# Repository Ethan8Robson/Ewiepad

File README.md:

# Ewiepad

A 6 key macropad built using an Arduino micro.

## Features
### PCB
Hot swappable switches through mill-max sockets
<br> Arduino Micro
<br> 3d printable case

### Case
Screws aren't visible on the front
<br> Flush design

## Parts List
1 Printed case (top + bottom)
<br> 1 PCB
<br> 1 Arduino micro
<br> 2 Screws of any kind as long as they fit
<br> 6 Bumpons to put on the bottom of the case
<br> 6 mechanical switches of any kind
<br> 12 mill max hotswap sockets

## Assembly
### Assembling the PCB
1 - First, gather the Arduino micro and PCB. They must be assembled together
<br> 2 - The Arduino must be placed UNDERNEATH the pcb, meaning it will be facing upside down. Solder all the pins to join the PCB and Arduino and then snip off the excess pin header coming from the Arduino micro.
<br> 3 - (Optional but very strongly recommended) If desired, place mill max sockets in each of the pins that the mechanical switches go and use a little bit of solder to seal them in. If not using mill max sockets, wait to solder the switches as that will be the last step.

### Putting Everything Together
1 - First, place the arduino into the top housing 
<br> 2 - Second, press the bottom housing into the top housing
<br> 3 - Join the 2 pieces together with the two screws
<br> 4 - Place the bumpons on the bottom of the keypad
<br> 5 - Upload the code to the arduino and get to using the macropad!

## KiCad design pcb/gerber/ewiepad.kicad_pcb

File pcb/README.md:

# PCB
## This section was created in honor of Daniel
### Front View

### Back View

### Ordering the PCB
To order the PCB, take the .zip file and upload it to your favorite PCB manufacturer. I used JLCpcb.

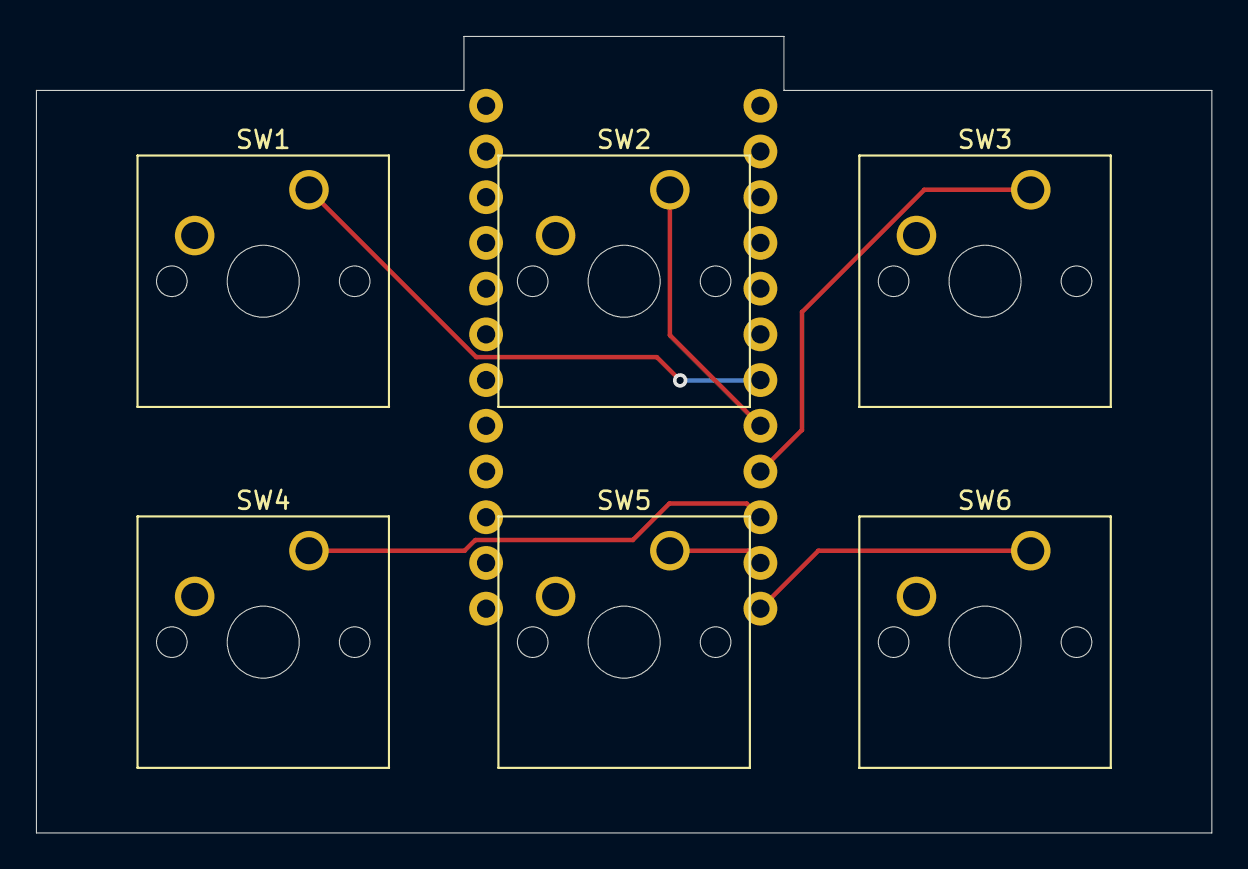
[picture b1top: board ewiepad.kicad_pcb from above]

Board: 2 copper layers, 65.3 x 44.3 mm, 7 parts (1 on the bottom side), 7 nets.

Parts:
B1: SPARKFUN_PRO_MICRO
SW1, SW2, SW3, SW4, SW5, SW6: SW_Push; SW_Cherry_MX_1.00u_PCB

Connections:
/sw1: B1.7, SW1.1
/sw2: B1.8, SW2.1
/sw3: B1.9, SW3.1
/sw4: B1.10, SW4.1
/sw5: B1.11, SW5.1
/sw6: B1.12, SW6.1
GND: B1.4, SW1.2, SW2.2, SW3.2, SW4.2, SW5.2, SW6.2

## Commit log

2021-09-12 Add case files
2021-09-12 Rename Ewiepad case.md to README.md
2021-09-12 Add pcb files
